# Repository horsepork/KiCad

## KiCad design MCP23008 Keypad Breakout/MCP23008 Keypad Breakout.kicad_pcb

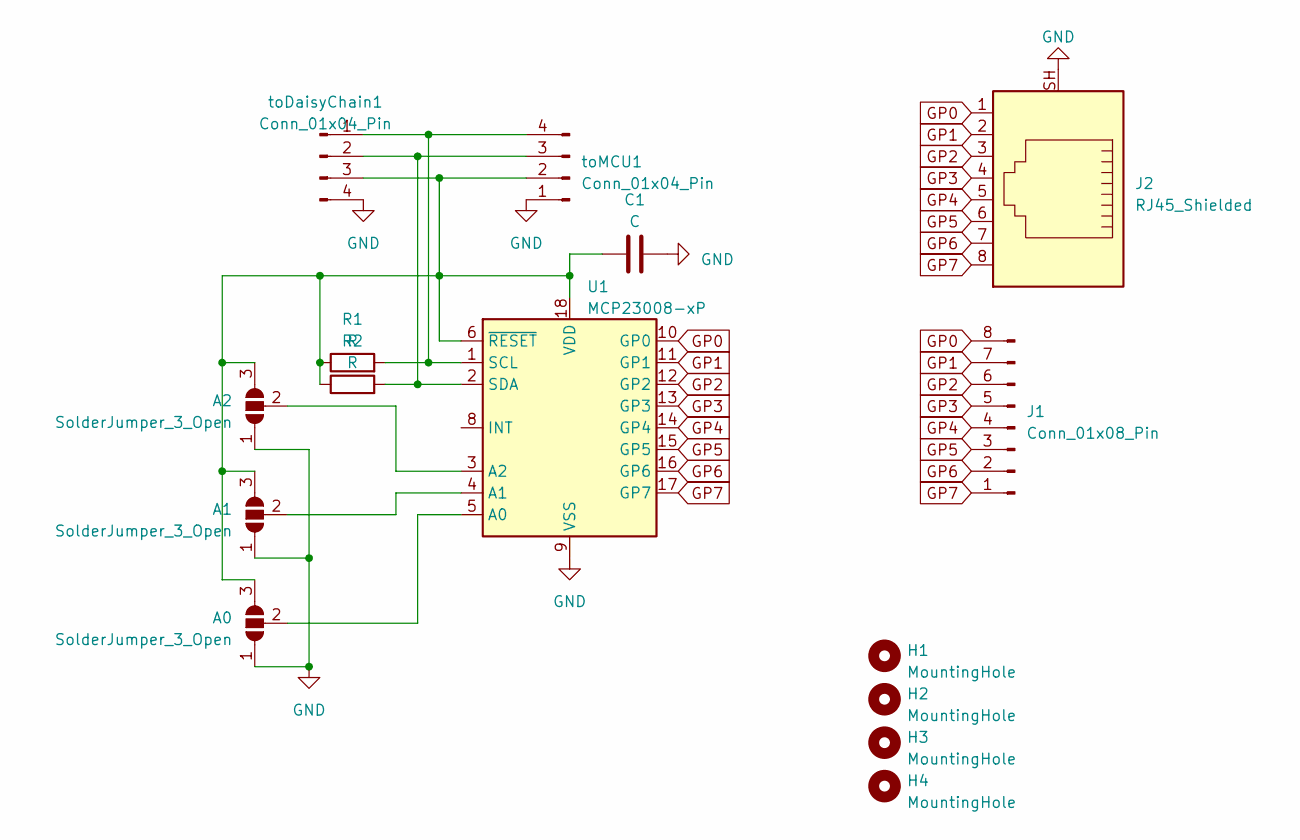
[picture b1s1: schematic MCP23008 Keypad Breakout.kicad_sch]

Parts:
A0, A1, A2: SolderJumper_3_Open; SolderJumper-3_P1.3mm_Open_RoundedPad1.0x1.5mm
C1: C; C_Disc_D4.3mm_W1.9mm_P5.00mm
H1, H2, H3, H4: MountingHole; MountingHole_3.2mm_M3
J1: Conn_01x08_Pin; Molex_KK-254_AE-6410-08A_1x08_P2.54mm_Vertical
J2: RJ45_Shielded; RJ45_Ninigi_GE
R1, R2: R; R_Axial_DIN0204_L3.6mm_D1.6mm_P7.62mm_Horizontal
U1: MCP23008-xP; DIP-18_W7.62mm
toDaisyChain1: Conn_01x04_Pin; Molex_KK-254_AE-6410-04A_1x04_P2.54mm_Vertical
toMCU1: Conn_01x04_Pin; Molex_KK-254_AE-6410-04A_1x04_P2.54mm_Vertical

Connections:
GND: A0.1 (A), A1.1 (A), A2.1 (A), C1.2, J2.SH, U1.9 (VSS), toDaisyChain1.4, toMCU1.1
GP0: J1.8, J2.1, U1.10 (GP0)
GP1: J1.7, J2.2, U1.11 (GP1)
GP2: J1.6, J2.3, U1.12 (GP2)
GP3: J1.5, J2.4, U1.13 (GP3)
GP4: J1.4, J2.5, U1.14 (GP4)
GP5: J1.3, J2.6, U1.15 (GP5)
GP6: J1.2, J2.7, U1.16 (GP6)
GP7: J1.1, J2.8, U1.17 (GP7)
unnamed: A0.3 (B), A1.3 (B), A2.3 (B), C1.1, R1.1, R2.1, U1.6 (~RESET), U1.18 (VDD), toDaisyChain1.3, toMCU1.2
unnamed: A0.2 (C), U1.5 (A0)
unnamed: A1.2 (C), U1.4 (A1)
unnamed: A2.2 (C), U1.3 (A2)
unnamed: R1.2, U1.1 (SCL), toDaisyChain1.1, toMCU1.4
unnamed: R2.2, U1.2 (SDA), toDaisyChain1.2, toMCU1.3

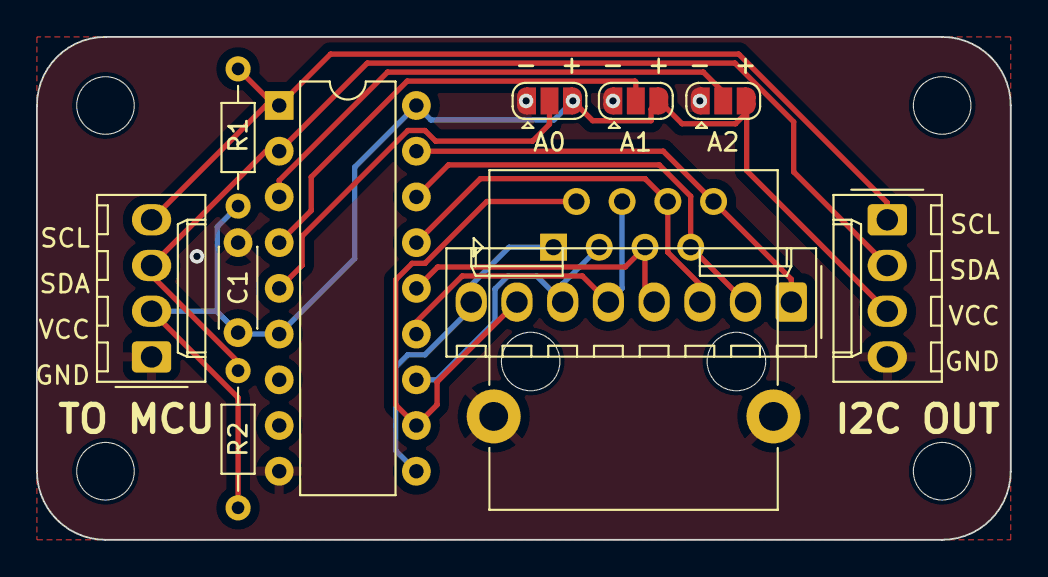
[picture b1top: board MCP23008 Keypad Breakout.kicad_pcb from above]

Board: 2 copper layers, 54.1 x 27.9 mm, 15 parts (0 on the bottom side), 15 nets.

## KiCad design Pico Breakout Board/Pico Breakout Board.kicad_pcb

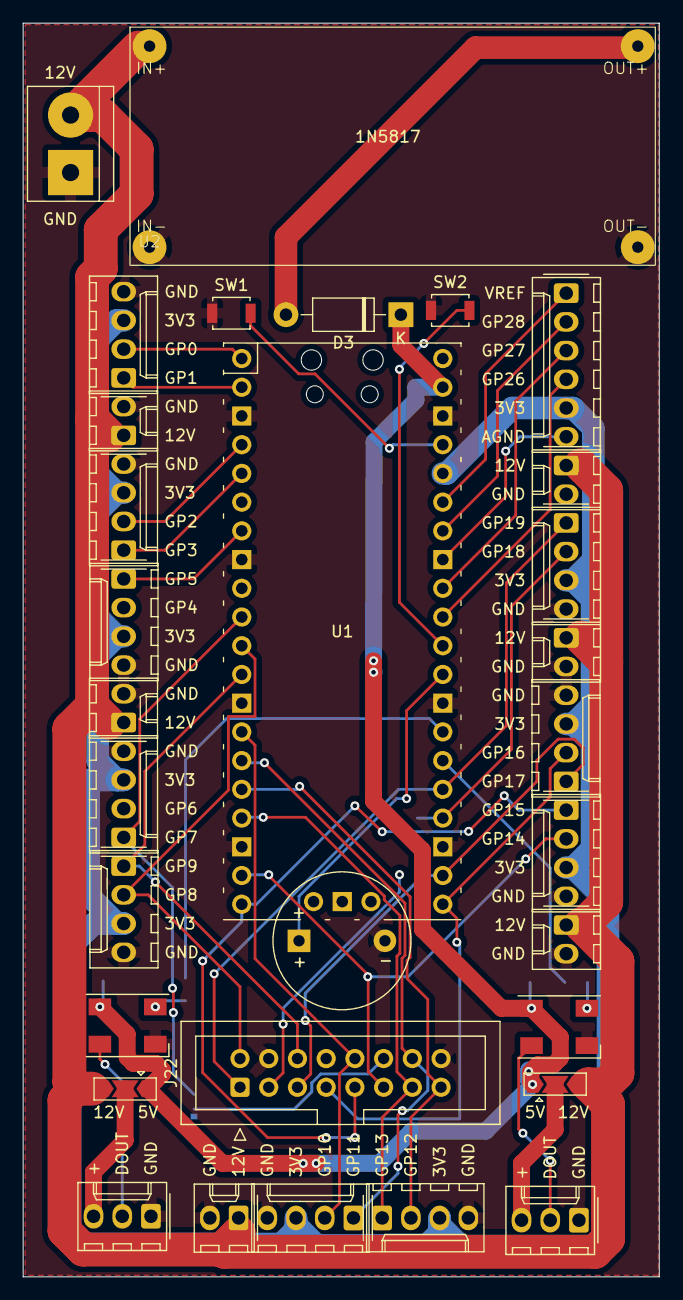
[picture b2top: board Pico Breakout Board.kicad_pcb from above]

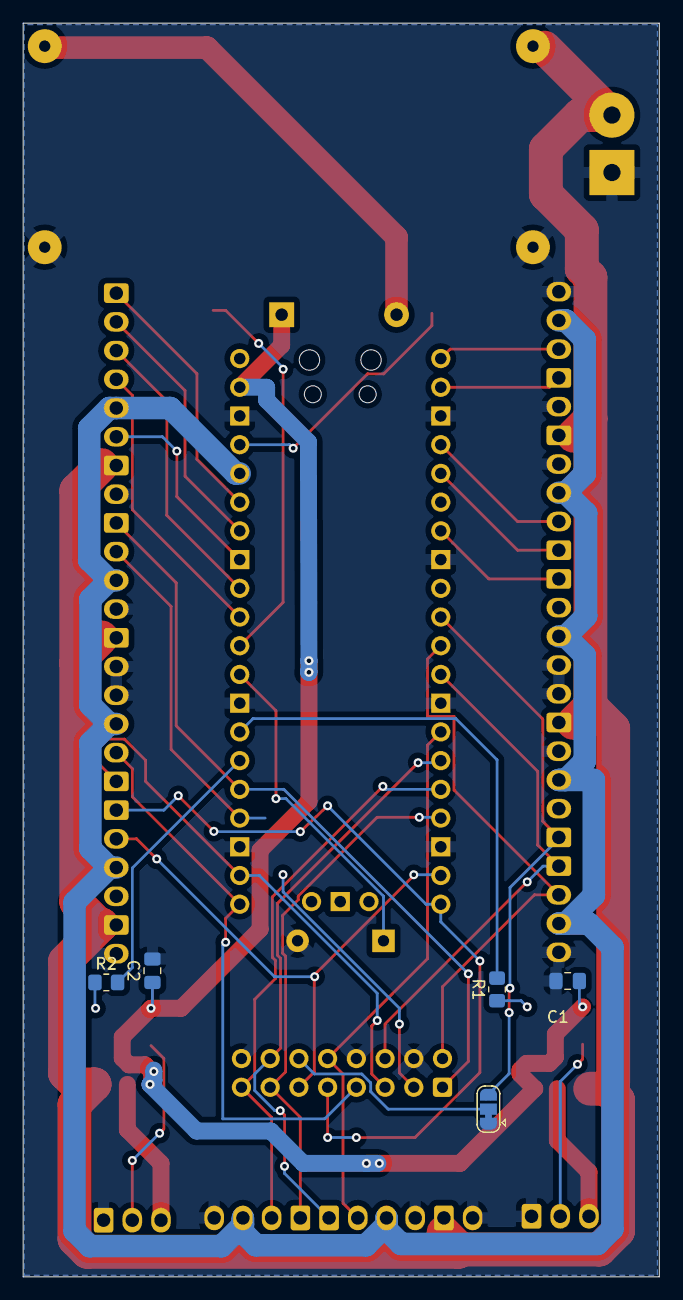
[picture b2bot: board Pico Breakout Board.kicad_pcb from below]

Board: 2 copper layers, 56.3 x 110.9 mm, 36 parts (5 on the bottom side), 42 nets.

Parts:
BZ1: Buzzer; Buzzer_12x9.5RM7.6
C1, C2: 100 nF; C_0805_2012Metric_Pad1.18x1.45mm_HandSolder
D1, D2: WS2812B; LED_WS2812B_PLCC4_5.0x5.0mm_P3.2mm
D3: 1N5817; D_DO-41_SOD81_P10.16mm_Horizontal
J1: screw terminal; TerminalBlock_bornier-2_P5.08mm
J2, J3: Conn_01x03_Pin; Molex_KK-254_AE-6410-03A_1x03_P2.54mm_Vertical
J4, J5: Conn_01x03_Pin; SolderJumper-3_P2.0mm_Open_TrianglePad1.0x1.5mm
J6, J7, J8, J9, J10, J14, J15, J17, J18, J20: Conn_01x04_Pin; Molex_KK-254_AE-6410-04A_1x04_P2.54mm_Vertical
J11, J12, J13, J16, J19, J21: Conn_01x02_Pin; Molex_KK-254_AE-6410-02A_1x02_P2.54mm_Vertical
J22: Conn_02x08_Counter_Clockwise; IDC-Header_2x08_P2.54mm_Vertical_CCW
J23: Conn_01x06_Pin; Molex_KK-254_AE-6410-06A_1x06_P2.54mm_Vertical
J24: Conn_01x03_Pin; SolderJumper-3_P1.3mm_Bridged12_RoundedPad1.0x1.5mm
R1, R2: 75; R_0805_2012Metric_Pad1.20x1.40mm_HandSolder
SW1, SW2: SW_Push; SW_SPST_B3U-1000P
U1: Pico; RPi_Pico_SMD_TH_No_Pads
U2: buck converter; LM2596 Buck Converter

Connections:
3V3: J6.3, J7.3, J8.3, J9.3, J10.3, J14.3, J15.3, J17.3, J18.3, J20.3, J23.5, U1.36 (3V3)
12V: J1.2, J4.3, J5.3, J11.1, J12.1, J13.1, J16.1, J19.1, J21.1, U2.1 (IN+)
ADV_VREF: J23.1, U1.35 (ADC_VREF)
AGND: J23.6, U1.33 (AGND)
GND: BZ1.2 (+), C1.2, C2.2, D1.3 (VSS), D2.3 (VSS), J1.1, J2.1, J3.1, J6.4, J7.4, J8.4, J9.4, J10.4, J11.2, J12.2, J13.2, J14.4, J15.4, J16.2, J17.4, J18.4, J19.2, J20.4, J21.2, J22.9, J22.13, J22.15, J24.1, SW1.1, SW2.1, U1.3 (GND), U1.8 (GND), U1.13 (GND), U1.18 (GND), U1.23 (GND), U1.28 (GND), U1.38 (GND), U2.2 (IN-), U2.4 (OUT-)
GPIO0: J6.2, U1.1 (GPIO0)
GPIO1: J6.1, U1.2 (GPIO1)
GPIO2: J7.2, U1.4 (GPIO2)
GPIO3: J7.1, U1.5 (GPIO3)
GPIO4: J8.2, U1.6 (GPIO4)
GPIO5: J8.1, U1.7 (GPIO5)
GPIO6: J9.2, U1.9 (GPIO6)
GPIO7: J9.1, J24.3, U1.10 (GPIO7)
GPIO8: J10.2, J22.16, U1.11 (GPIO8)
GPIO9: J10.1, J22.14, U1.12 (GPIO9)
GPIO10: J14.2, J22.12, U1.14 (GPIO10)
GPIO11: J14.1, J22.10, U1.15 (GPIO11)
GPIO12: J15.2, J22.8, U1.16 (GPIO12)
GPIO13: J15.1, J22.7, U1.17 (GPIO13)
GPIO14: J17.2, J22.6, U1.19 (GPIO14)
GPIO15: J17.1, J22.5, U1.20 (GPIO15)
GPIO16: J18.2, J22.4, U1.21 (GPIO16)
GPIO17: J18.1, J22.3, U1.22 (GPIO17)
GPIO18: J20.2, J22.2, U1.24 (GPIO18)
GPIO19: J20.1, J22.1, U1.25 (GPIO19)
GPIO26: J23.4, U1.31 (GPIO26_ADC0)
GPIO27: J23.3, U1.32 (GPIO27_ADC1)
GPIO28: J23.2, U1.34 (GPIO28_ADC2)
unnamed: BZ1.1 (-), U1.29 (GPIO22)
unnamed: D1.4 (DIN), R1.1
unnamed: D1.2 (DOUT), J2.2
unnamed: C1.1, C2.1, D1.1 (VDD), D2.1 (VDD), D3.1 (K), J4.1, J5.1, U1.39 (VSYS)
unnamed: D2.4 (DIN), R2.1
unnamed: D2.2 (DOUT), J3.2
unnamed: D3.2 (A), U2.3 (OUT+)
unnamed: J2.3, J4.2
unnamed: J3.3, J5.2
unnamed: J22.11, J24.2
unnamed: SW1.2, U1.37 (3V3_EN)
unnamed: R2.2, U1.26 (GPIO20)
unnamed: R1.2, U1.27 (GPIO21)
unnamed: SW2.2, U1.30 (RUN)

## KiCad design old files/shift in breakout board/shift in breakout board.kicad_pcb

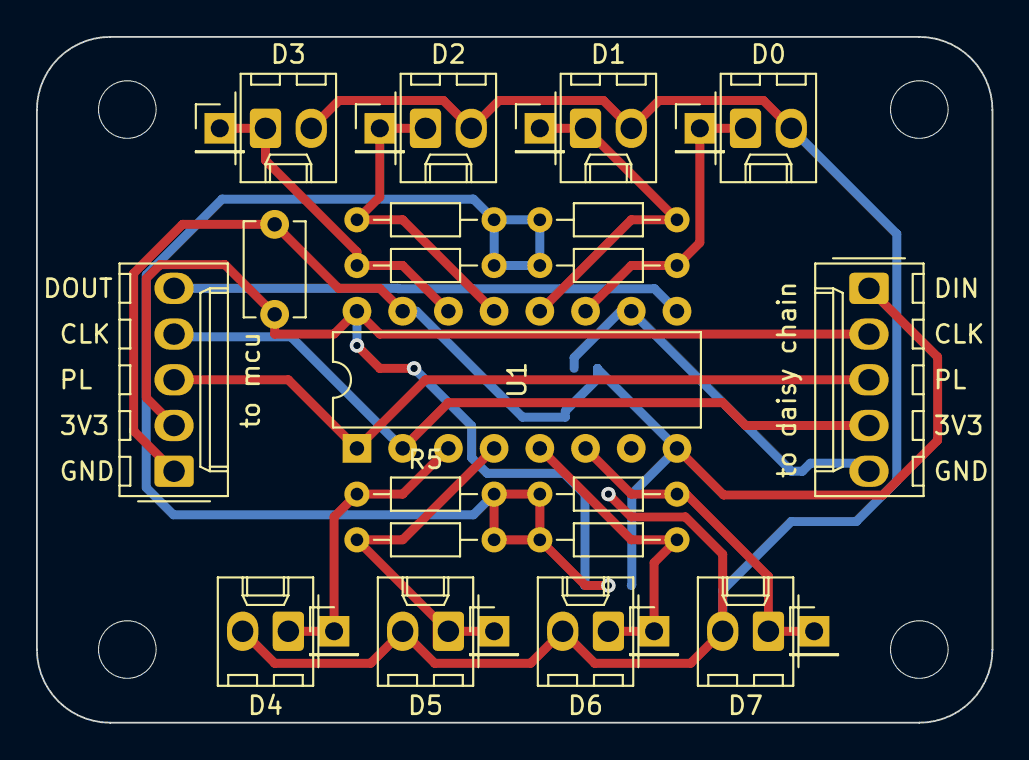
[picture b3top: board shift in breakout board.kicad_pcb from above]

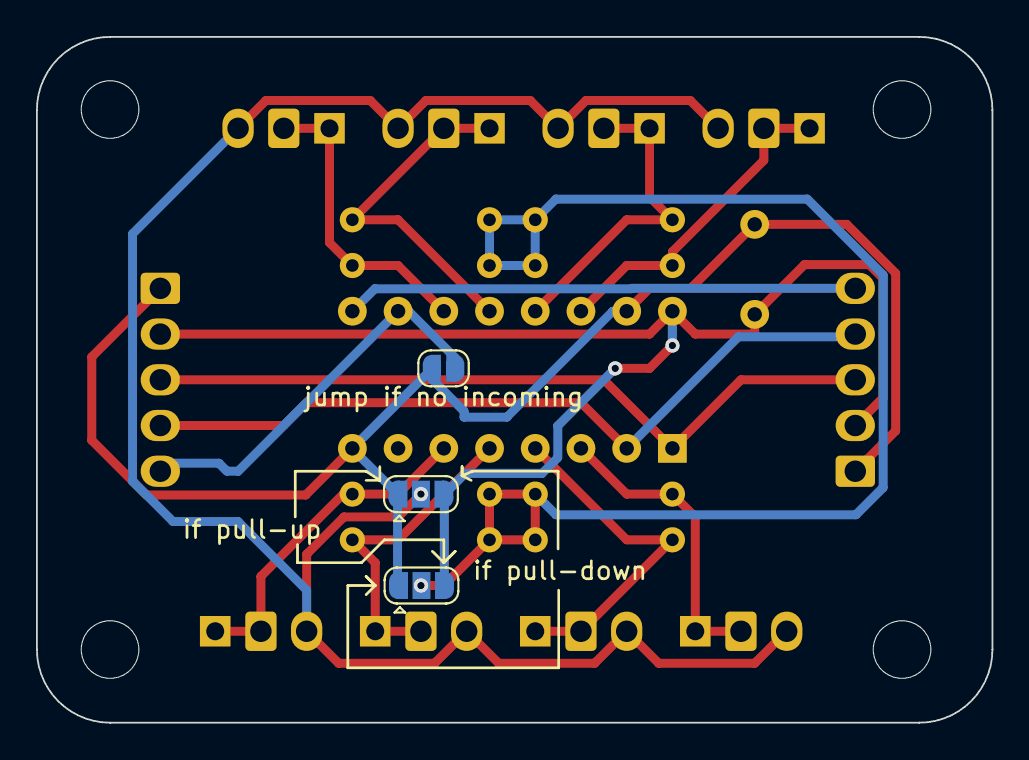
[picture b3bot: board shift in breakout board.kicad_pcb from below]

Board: 2 copper layers, 53.1 x 38.1 mm, 35 parts (3 on the bottom side), 16 nets.

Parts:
C1: C; C_Disc_D5.1mm_W3.2mm_P5.00mm
D0, D1, D2, D3, D4, D5, D6, D7: Conn_01x02_Pin; Molex_KK-254_AE-6410-02A_1x02_P2.54mm_Vertical
H1, H2, H3, H4: MountingHole; MountingHole_3.2mm_M3
J10, J11, J12, J13, J14, J15, J16, J17: Conn_01x01_Pin; PinHeader_1x01_P2.54mm_Vertical
R1, R2, R3, R4, R5, R6, R7, R8: 4.7k; R_Axial_DIN0204_L3.6mm_D1.6mm_P7.62mm_Horizontal
U1: 74HC165; DIP-16_W7.62mm
connectorSide1: Conn_01x03_Pin; SolderJumper-3_P1.3mm_Open_RoundedPad1.0x1.5mm
jumpIfNoIncoming1: Conn_01x02_Pin; SolderJumper-2_P1.3mm_Open_RoundedPad1.0x1.5mm
resistorSide1: Conn_01x03_Pin; SolderJumper-3_P1.3mm_Open_RoundedPad1.0x1.5mm
toDaisyChain1: Conn_01x05_Pin; Molex_KK-254_AE-6410-05A_1x05_P2.54mm_Vertical
toMCU1: Conn_01x05_Pin; Molex_KK-254_AE-6410-05A_1x05_P2.54mm_Vertical

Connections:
GND: C1.2, U1.8 (GND), U1.15 (~CE), connectorSide1.1, jumpIfNoIncoming1.1, resistorSide1.1, toDaisyChain1.1, toMCU1.1
unnamed: D0.1, J10.1, R1.1, U1.11 (D0)
unnamed: D0.2, D1.2, D2.2, D3.2, D4.2, D5.2, D6.2, D7.2, connectorSide1.2
unnamed: D1.1, J11.1, R2.1, U1.12 (D1)
unnamed: D2.1, J12.1, R3.1, U1.13 (D2)
unnamed: D3.1, J13.1, R4.1, U1.14 (D3)
unnamed: D4.1, J14.1, R5.1, U1.3 (D4)
unnamed: D5.1, J15.1, R6.1, U1.4 (D5)
unnamed: D6.1, J16.1, R7.1, U1.5 (D6)
unnamed: D7.1, J17.1, R8.1, U1.6 (D7)
unnamed: U1.2 (CP), toDaisyChain1.4, toMCU1.4
unnamed: U1.10 (DS), jumpIfNoIncoming1.2, toDaisyChain1.5
unnamed: U1.9 (Q7), toMCU1.5
unnamed: C1.1, U1.16 (VCC), connectorSide1.3, resistorSide1.3, toDaisyChain1.2, toMCU1.2
unnamed: U1.1 (~PL), toDaisyChain1.3, toMCU1.3
unnamed: R1.2, R2.2, R3.2, R4.2, R5.2, R6.2, R7.2, R8.2, resistorSide1.2
